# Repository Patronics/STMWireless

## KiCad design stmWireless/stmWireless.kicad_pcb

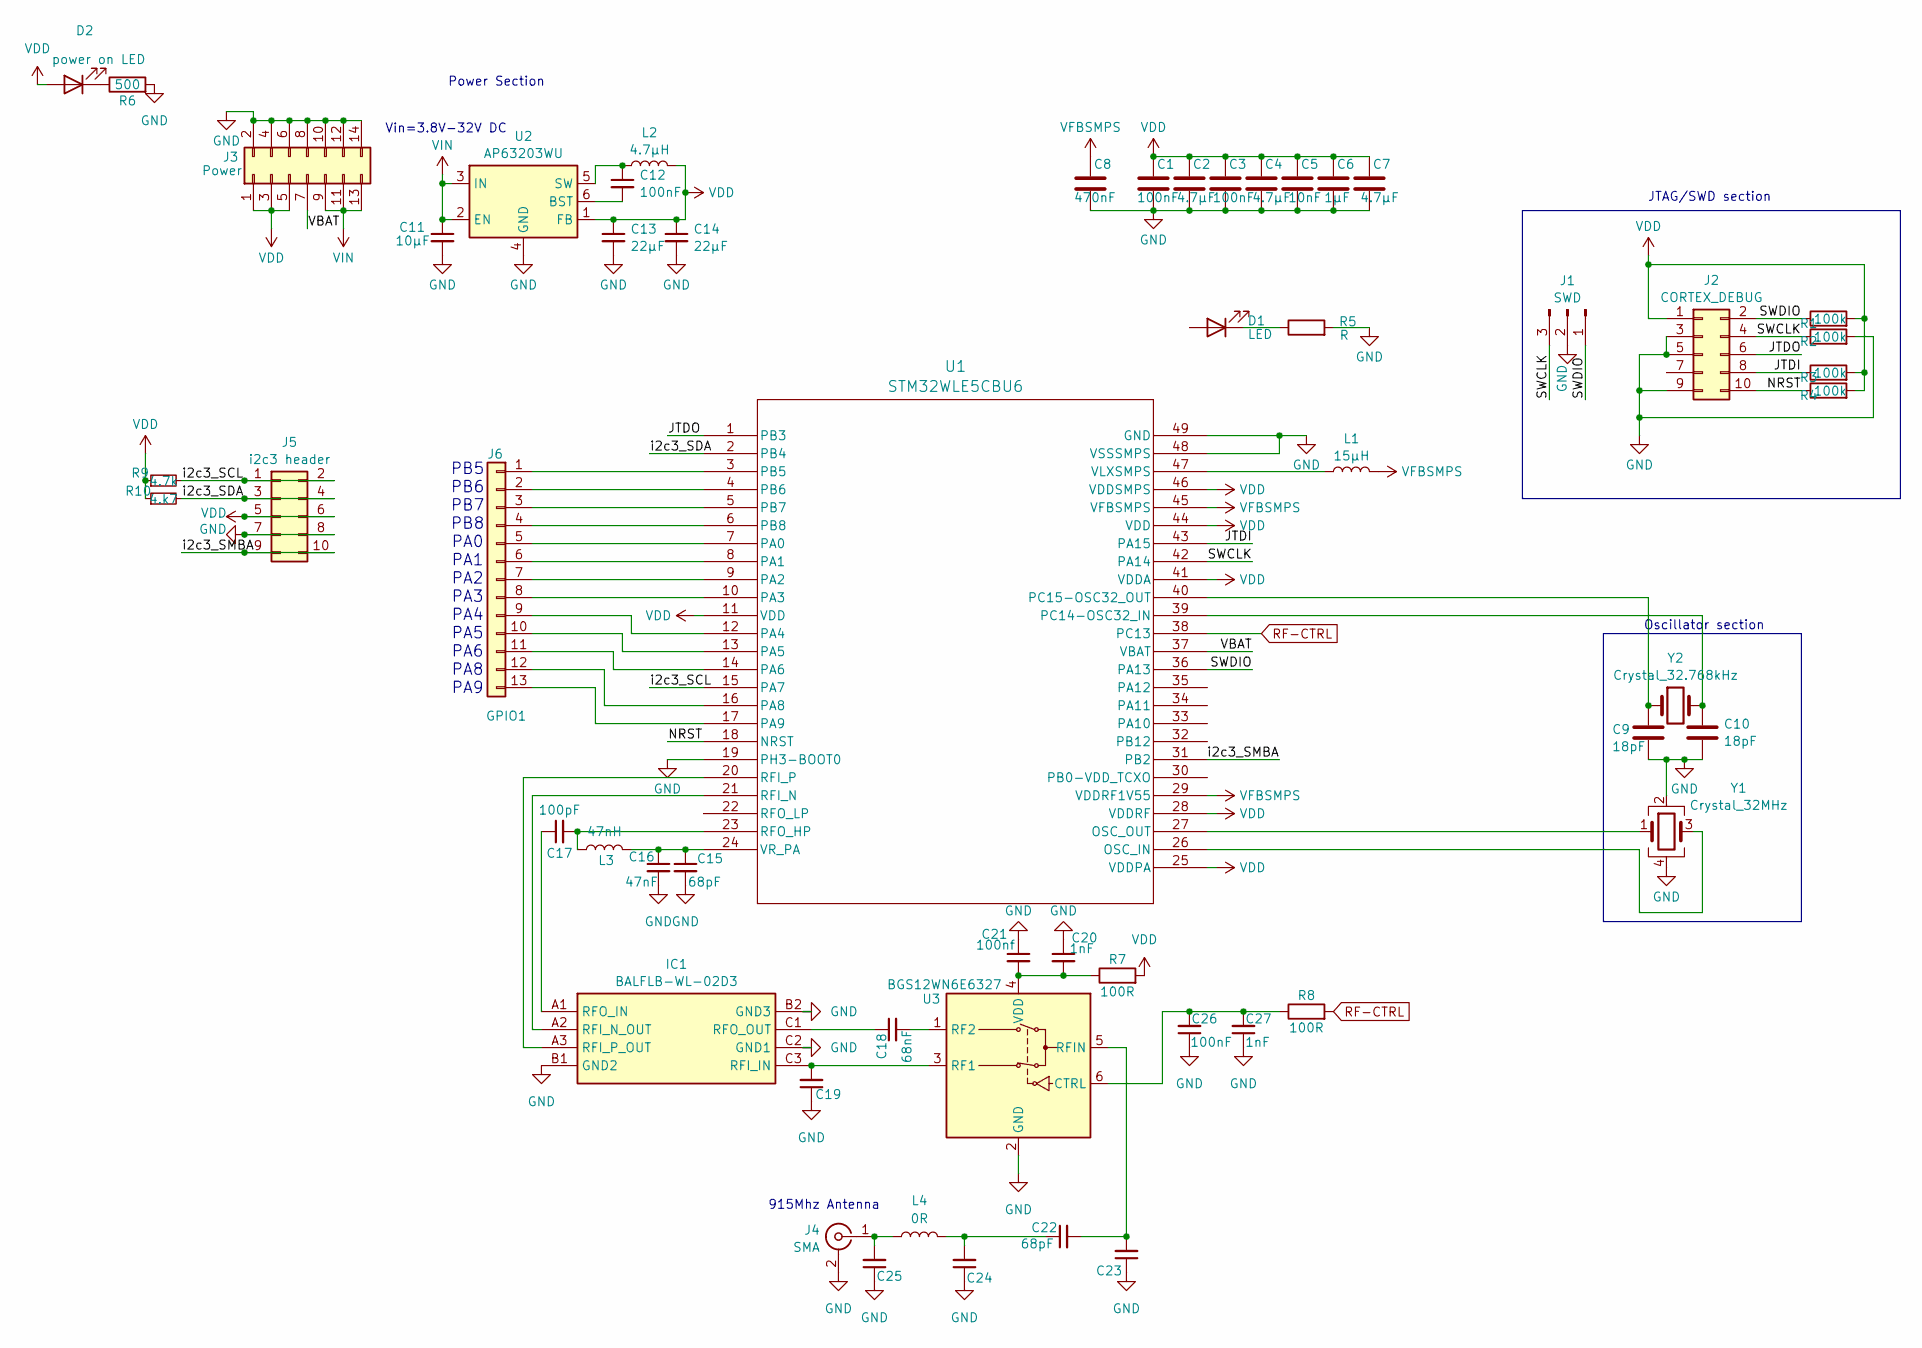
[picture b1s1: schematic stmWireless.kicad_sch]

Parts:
C1, C3, C12, C26: 100nF; C_0603_1608Metric
C2, C4, C7: 4.7µF; C_0603_1608Metric
C5: 10nF; C_0603_1608Metric
C6: 1µF; C_0603_1608Metric
C8: 470nF; C_0603_1608Metric
C9, C10: 18pF; C_0603_1608Metric
C11: 10µF; C_0603_1608Metric
C13, C14: 22µF; C_0603_1608Metric
C15, C22: 68pF; C_0603_1608Metric
C16: 47nF; C_0603_1608Metric
C17: 100pF; C_0603_1608Metric
C18: 68nF; C_0603_1608Metric
C19, C23, C24, C25: C_0603_1608Metric
C20, C27: 1nF; C_0603_1608Metric
C21: 100nf; C_0603_1608Metric
D1: LED; LED_0603_1608Metric
D2: power on LED; LED_0603_1608Metric
IC1: BALFLB-WL-02D3; BALFHBWL02D3; Manufacturer_Part_Number BALFHB-WL-02D3; Mouser Part Number 511-BALFHB-WL-02D3
J1: SWD; PinHeader_1x03_P2.54mm_Vertical
J2: CORTEX_DEBUG; PinHeader_2x05_P2.54mm_Vertical
J3: Power; PinHeader_2x07_P2.54mm_Vertical
J4: SMA
J5: i2c3 header; PinHeader_2x05_P2.54mm_Vertical
J6: GPIO1; PinHeader_1x13_P2.54mm_Vertical
L1: 15µH; L_0603_1608Metric
L2: 4.7µH; L_0603_1608Metric
L3: 47nH; L_0603_1608Metric
L4: 0R; L_0603_1608Metric
R1, R2, R3, R4: 100k; R_0603_1608Metric
R5: R; R_0603_1608Metric
R6: 500; R_0603_1608Metric
R7, R8: 100R; R_0603_1608Metric
R9: 4.7k; R_0603_1608Metric
R10: 4.k7; R_0603_1608Metric
U1: STM32WLE5CBU6; UFQFPN48_7X7_STM
U2: AP63203WU; TSOT-23-6
U3: BGS12WN6E6327; Infineon_PG-TSNP-6-10_0.7x1.1mm_0.7x1.1mm_P0.4mm
Y1: Crystal_32MHz; Crystal_SMD_2016-4Pin_2.0x1.6mm
Y2: Crystal_32.768kHz; Crystal_SMD_3215-2Pin_3.2x1.5mm

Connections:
/JTDI: J2.8, R3.1, U1.43 (PA15)
/JTDO: J2.6, U1.1 (PB3)
/NRST: J2.10, R4.1, U1.18 (NRST)
/SWCLK: J1.3, J2.4, R2.1, U1.42 (PA14)
/SWDIO: J1.1, J2.2, R1.1, U1.36 (PA13)
/VBAT: J3.7, U1.37 (VBAT)
/i2c3_SCL: J5.1, J5.2, R9.2, U1.15 (PA7)
/i2c3_SDA: J5.3, J5.4, R10.2, U1.2 (PB4)
/i2c3_SMBA: J5.9, J5.10, U1.31 (PB2)
GND: C1.2, C2.2, C3.2, C4.2, C5.2, C6.2, C7.2, C8.2, C9.2, C10.2, C11.2, C13.2, C14.2, C15.2, C16.2, C19.1, C20.1, C21.1, C23.1, C24.1, C25.1, C26.1, C27.1, IC1.B1 (GND2), IC1.B2 (GND3), IC1.C2 (GND1), J1.2, J2.3, J2.5, J2.9, J3.2, J3.4, J3.6, J3.8, J3.10, J3.12, J3.14, J4.2 (Ext), J5.7, J5.8, R2.2, R5.2, R6.2, U1.19 (PH3-BOOT0), U1.48 (VSSSMPS), U1.49 (GND), U2.4 (GND), U3.2 (GND), Y1.2, Y1.4
unnamed: C22.1, C24.2, L4.2
unnamed: D1.1 (K), R5.1
unnamed: D2.1 (K), R6.1
unnamed: C19.2, IC1.C3 (RFI_IN), U3.3 (RF1)
unnamed: C17.1, IC1.A1 (RFO_IN)
unnamed: C18.1, IC1.C1 (RFO_OUT)
unnamed: C25.2, J4.1 (In), L4.1
unnamed: J6.1, U1.3 (PB5)
unnamed: J6.2, U1.4 (PB6)
unnamed: J6.3, U1.5 (PB7)
unnamed: J6.4, U1.6 (PB8)
unnamed: J6.5, U1.7 (PA0)
unnamed: J6.6, U1.8 (PA1)
unnamed: J6.7, U1.9 (PA2)
unnamed: J6.8, U1.10 (PA3)
unnamed: J6.9, U1.12 (PA4)
unnamed: J6.10, U1.13 (PA5)
unnamed: J6.11, U1.14 (PA6)
unnamed: J6.12, U1.16 (PA8)
unnamed: J6.13, U1.17 (PA9)
unnamed: U1.26 (OSC_IN), Y1.3
unnamed: U1.27 (OSC_OUT), Y1.1
unnamed: C10.1, U1.39 (PC14-OSC32_IN), Y2.2
unnamed: C9.1, U1.40 (PC15-OSC32_OUT), Y2.1
unnamed: C17.2, L3.1, U1.23 (RFO_HP)
unnamed: L1.1, U1.47 (VLXSMPS)
unnamed: C15.1, C16.1, L3.2, U1.24 (VR_PA)
unnamed: C12.2, U2.6 (BST)
unnamed: C12.1, L2.1, U2.5 (SW)
unnamed: C26.2, C27.2, R8.1, U3.6 (CTRL)
unnamed: C18.2, U3.1 (RF2)
unnamed: C22.2, C23.2, U3.5 (RFIN)
unnamed: C20.2, C21.2, R7.1, U3.4 (VDD)
Net-IC1-RFI_N: IC1.A2 (RFI_N_OUT), U1.21 (RFI_N)
Net-IC1-RFI_P: IC1.A3 (RFI_P_OUT), U1.20 (RFI_P)
RF-CTRL: R8.2, U1.38 (PC13)
VDD: C1.1, C2.1, C3.1, C4.1, C5.1, C6.1, C7.1, C13.1, C14.1, D2.2 (A), J2.1, J3.1, J3.3, J3.5, J5.5, J5.6, L2.2, R1.2, R3.2, R4.2, R7.2, R9.1, R10.1, U1.11 (VDD), U1.25 (VDDPA), U1.28 (VDDRF), U1.41 (VDDA), U1.44 (VDD), U1.46 (VDDSMPS), U2.1 (FB)
VFBSMPS: C8.1, L1.2, U1.29 (VDDRF1V55), U1.45 (VFBSMPS)
VIN: C11.1, J3.9, J3.11, J3.13, U2.2 (EN), U2.3 (IN)

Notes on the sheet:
Vin=3.8V-32V DC
Power Section
915Mhz Antenna
JTAG/SWD section
Oscillator section
PB5 PB6 PB7 PB8 PA0 PA1 PA2 PA3 PA4 PA5 PA6 PA8 PA9

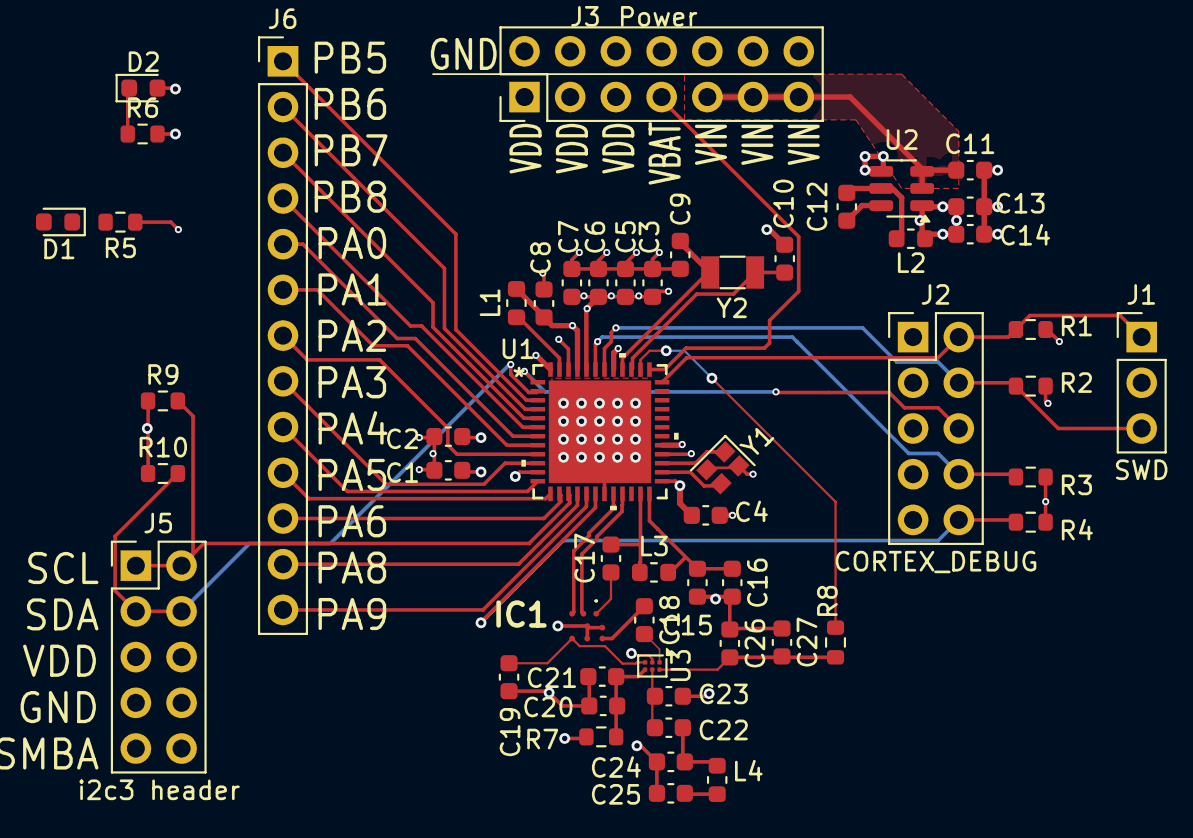
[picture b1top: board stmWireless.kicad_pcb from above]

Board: 4 copper layers, 54 parts (0 on the bottom side), 49 nets.

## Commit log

2024-07-04 add power supply components to PCB
2024-07-05 added power LED
2024-07-17 begining of wireless thing
2024-07-17 add schematic item for BALF IPD
2024-07-17 add required PCB Footprint
2024-07-17 more wiorless
2024-07-17 coped RF cercit from refres scamatic 1848
2024-07-17 assign footprints and minor cleanup
2024-07-17 move components badly into place
2024-07-17 unorginised phisical PCB layout
2024-07-17 substitute IPD to fix freqency
2024-07-18 fix backwards antenna
2024-08-08 add big reference manual that explains a lot and label 915mhz antenna
2024-08-08 add additional application notes for wireless documentation
2024-08-08 add markdown table of documentation links
2024-08-08 Fix broken link formatting
2024-08-08 improve layout for power header and voltage regulator, and add i2c3 header
2024-08-08 fix zone fill for vin layer
2024-08-08 remove uneeded autosave file
2024-08-09 add GPIO port of most unused pins
2024-08-09 rotate crystal to shorten traces and clear space, and resolve many DRC issues
2024-08-09 add start of GPIO pin labling (todo also lable features such as USARTRX/TX)
2024-08-13 improve highlighted notes on datasheet, and add additional reference about impedance matching networks. Also add pin labels to schematic and PCB GPIO pins
2025-01-22 initial layout of radio portion, add another reference design with BOM. still need to adjust impedance and add connector
